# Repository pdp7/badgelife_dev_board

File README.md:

## For Defcon 27 SAO v1.69bis (6-pin version):
  * [What is badge add-on v1.69bis standard?](https://hackaday.com/2019/03/20/introducing-the-shitty-add-on-v1-69bis-standard/)
  * Design files are in [branch v1.69bis](https://github.com/OSHPark/badgelife_dev_board/tree/v169bis)
  * Full version: [badgelife_v169bis_proto_v1.kicad_pcb](https://github.com/OSHPark/badgelife_dev_board/blob/v169bis/badgelife_v169bis_proto_v1.kicad_pcb)
    * [OSH Park shared project](https://oshpark.com/projects/kT4eHBn0)
  * Compact version: [badgelife_v169bis_proto_v2.kicad_pcb](https://github.com/OSHPark/badgelife_dev_board/blob/v169bis/badgelife_v169bis_proto_v2.kicad_pcb)
    * [OSH Park shared project](https://oshpark.com/projects/2MfjzgRb)

## OHS18 badge add-on dev board

* [Open Hardware Summit 2018 badge](http://oshwabadge2018.github.io) add-on prototype dev board
* KiCad file: [ohs18_dev_board.kicad_pcb](ohs18_dev_board.kicad_pcb)
* [OSH Park shared project](https://oshpark.com/shared_projects/sE4DJMR1)
* Designed by ANDnXOR for DefCon 26 #badgelife add-on standard (DC26 SAO):
  * [original GitHub repo](https://github.com/ANDnXOR/badgelife_dev_board)
  * [Hackaday.io project log](https://hackaday.io/project/52950-shitty-add-ons/log/139892-badgelife-dc26-shitty-development-board)

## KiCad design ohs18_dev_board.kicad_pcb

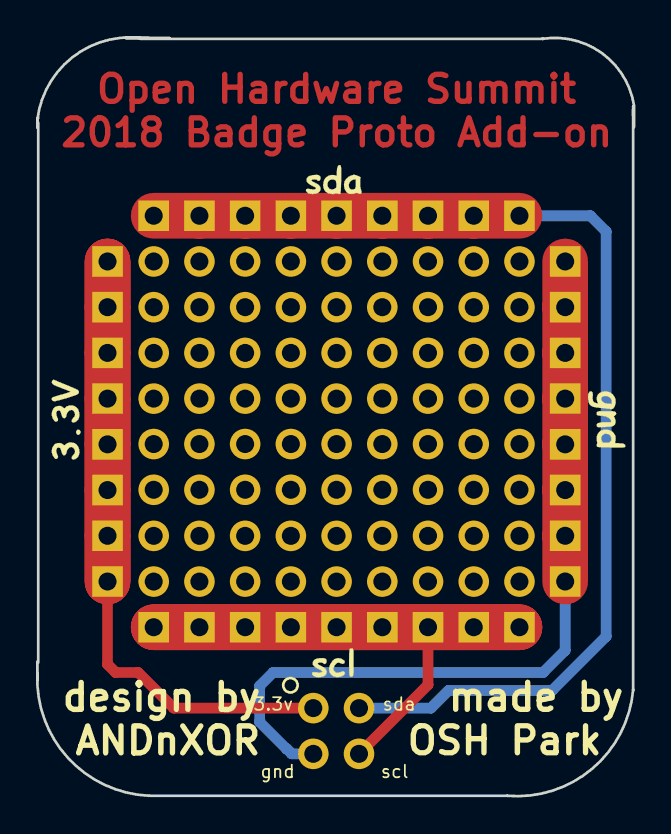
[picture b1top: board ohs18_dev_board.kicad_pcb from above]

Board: 2 copper layers, 33.2 x 42.2 mm, 5 parts (0 on the bottom side), 4 nets.

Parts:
J1, J2: Conn_01x08; Power_Rail-01x08
J3, J4: Conn_01x09; Power_Rail-01x09
X1: Badgelife_shitty_connector; Badgelife-Shitty-2x2

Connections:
+3V3: J1.1, J1.2, J1.3, J1.4, J1.5, J1.6, J1.7, J1.8, X1.1
GND: J2.1, J2.2, J2.3, J2.4, J2.5, J2.6, J2.7, J2.8, X1.2
SCL: J4.1, J4.2, J4.3, J4.4, J4.5, J4.6, J4.7, J4.8, J4.9, X1.3
SDA: J3.1, J3.2, J3.3, J3.4, J3.5, J3.6, J3.7, J3.8, J3.9, X1.4

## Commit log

2018-08-06 add simple BioHacking Village artwork to add-on board
2018-08-15 add rounded corner prototype board
2018-08-22 work in progress
2018-09-01 add Open Hardware Summit 2018 version
2019-07-31 add badgelife add-on proto board for the SAO v1.69bis standard
